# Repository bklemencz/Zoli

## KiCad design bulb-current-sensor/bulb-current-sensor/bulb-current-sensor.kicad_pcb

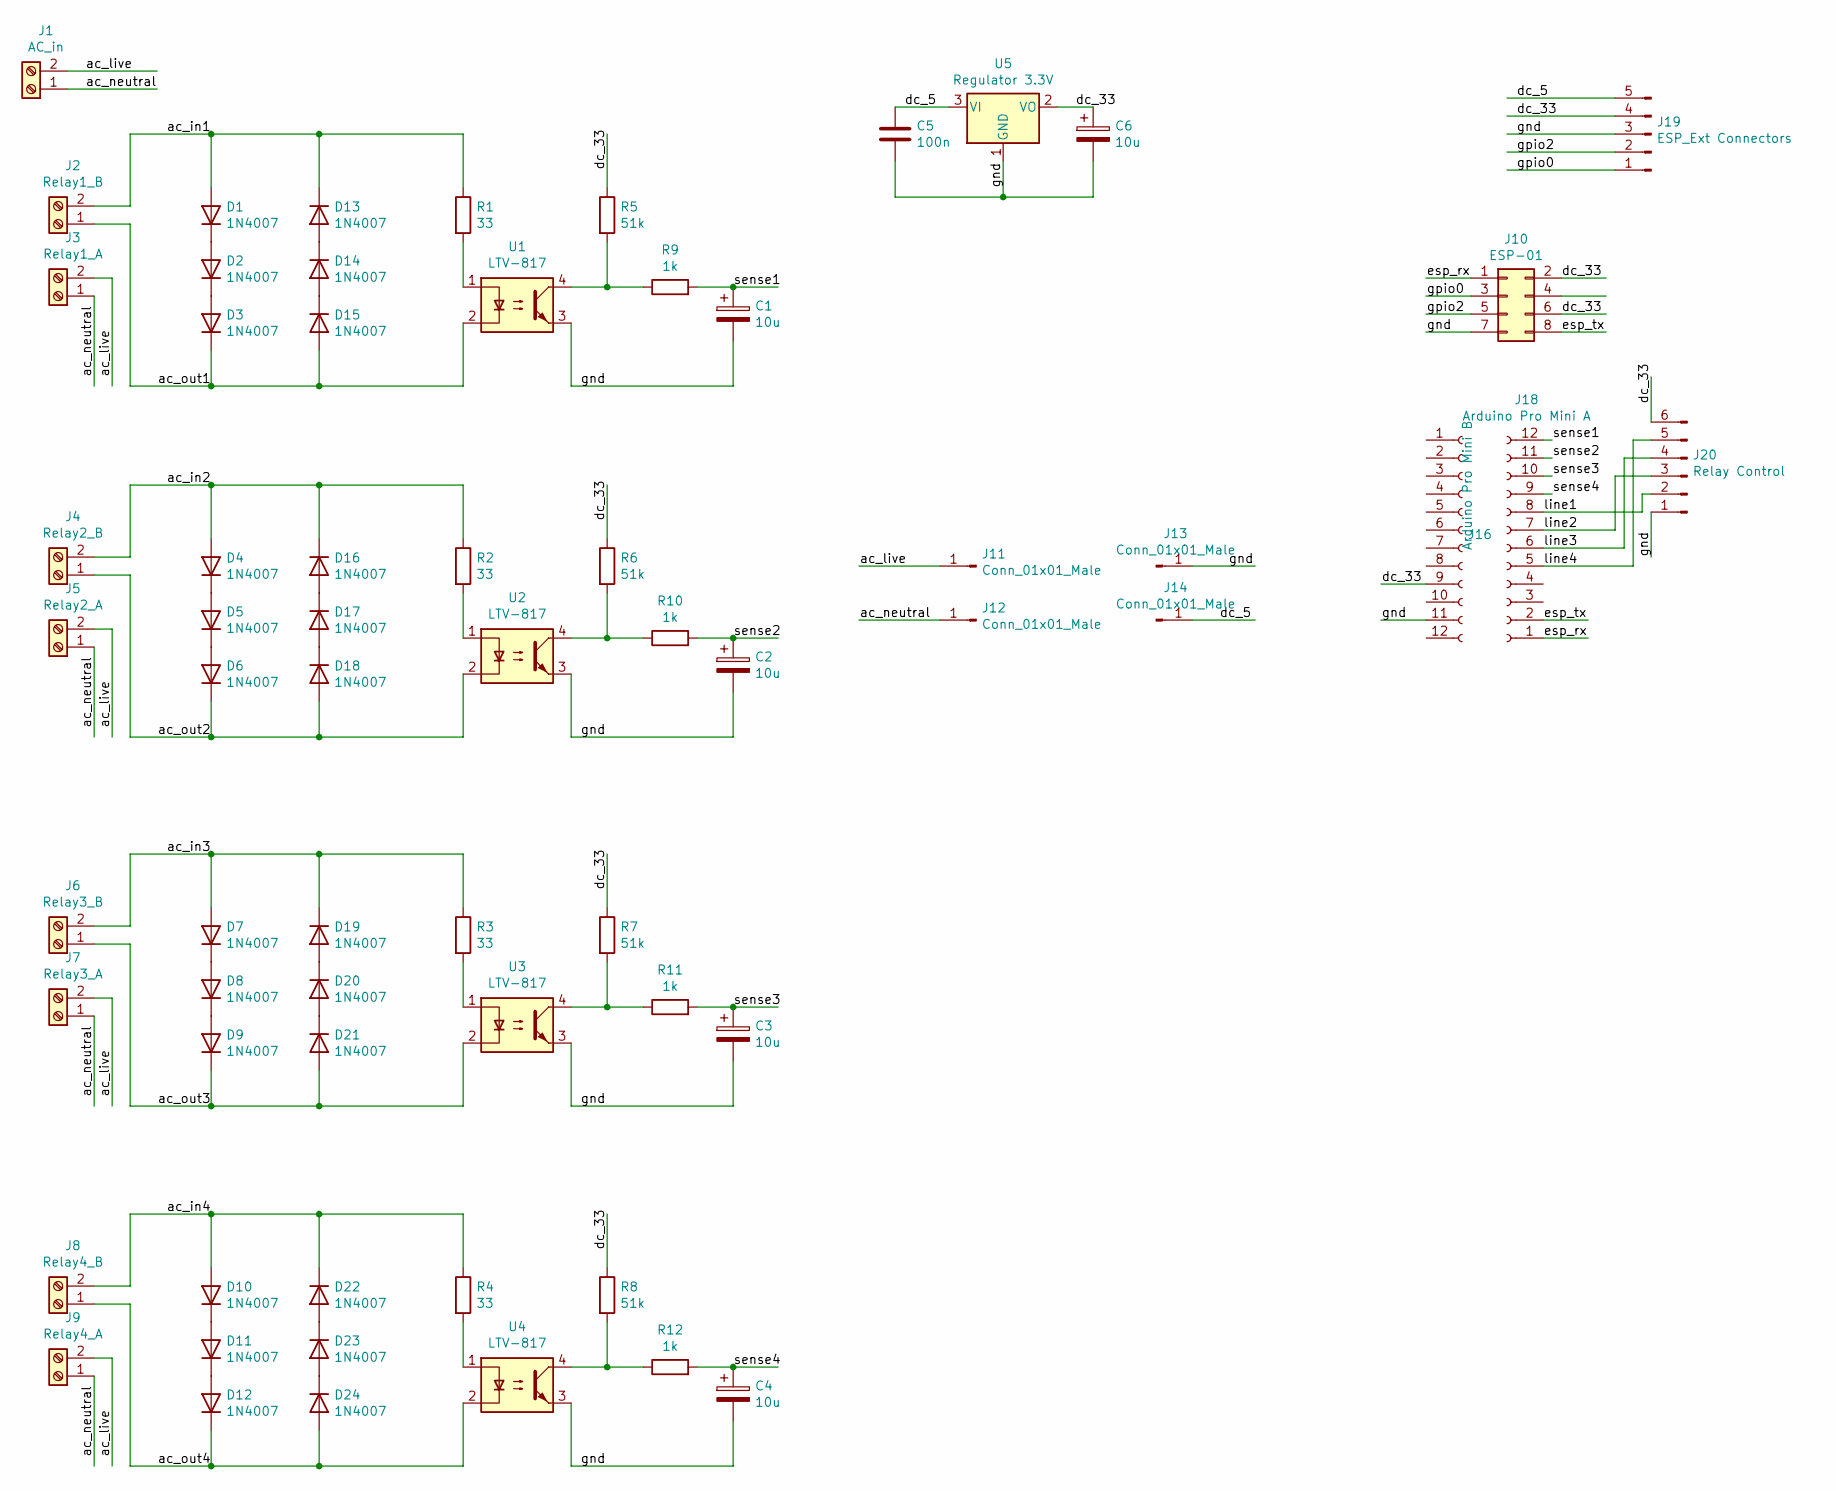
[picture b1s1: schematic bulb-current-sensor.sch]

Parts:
C1, C2, C3, C4: 10u; CP_Radial_D5.0mm_P2.50mm
C5: 100n; C_Disc_D3.0mm_W1.6mm_P2.50mm
C6: 10u; CP_Radial_D4.0mm_P1.50mm
D1, D2, D3, D4, D5, D6, D7, D8, D9, D10, D11, D12, D13, D14, D15, D16, D17, D18, D19, D20, D21, D22, D23, D24: 1N4007; D_DO-41_SOD81_P10.16mm_Horizontal
J1: AC_in; TerminalBlock_bornier-2_P5.08mm
J2: Relay1_B; TerminalBlock_bornier-2_P5.08mm
J3: Relay1_A; TerminalBlock_bornier-2_P5.08mm
J4: Relay2_B; TerminalBlock_bornier-2_P5.08mm
J5: Relay2_A; TerminalBlock_bornier-2_P5.08mm
J6: Relay3_B; TerminalBlock_bornier-2_P5.08mm
J7: Relay3_A; TerminalBlock_bornier-2_P5.08mm
J8: Relay4_B; TerminalBlock_bornier-2_P5.08mm
J9: Relay4_A; TerminalBlock_bornier-2_P5.08mm
J10: ESP-01; PinHeader_2x04_P2.54mm_Vertical
J11, J12, J13, J14: Conn_01x01_Male; PinHeader_1x01_P2.54mm_Vertical
J16: Arduino Pro Mini B; PinHeader_1x12_P2.54mm_Vertical
J18: Arduino Pro Mini A; PinHeader_1x12_P2.54mm_Vertical
J19: ESP_Ext Connectors; PinHeader_1x05_P2.54mm_Vertical
J20: Relay Control; PinHeader_1x06_P2.54mm_Vertical
R1, R2, R3, R4: 33; R_Axial_DIN0207_L6.3mm_D2.5mm_P10.16mm_Horizontal
R5, R6, R7, R8: 51k; R_Axial_DIN0204_L3.6mm_D1.6mm_P7.62mm_Horizontal
R9, R10, R11, R12: 1k; R_Axial_DIN0204_L3.6mm_D1.6mm_P7.62mm_Horizontal
U1, U2, U3, U4: LTV-817; DIP-4_W7.62mm
U5: Regulator 3.3V; TO-220-3_Vertical

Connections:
/ac_in1: D1.2 (A), D13.1 (K), J2.2, R1.1
/ac_in2: D4.2 (A), D16.1 (K), J4.2, R2.1
/ac_in3: D7.2 (A), D19.1 (K), J6.2, R3.1
/ac_in4: D10.2 (A), D22.1 (K), J8.2, R4.1
/ac_live: J1.2, J3.2, J5.2, J7.2, J9.2, J11.1
/ac_neutral: J1.1, J3.1, J5.1, J7.1, J9.1, J12.1
/ac_out1: D3.1 (K), D15.2 (A), J2.1, U1.2
/ac_out2: D6.1 (K), D18.2 (A), J4.1, U2.2
/ac_out3: D9.1 (K), D21.2 (A), J6.1, U3.2
/ac_out4: D12.1 (K), D24.2 (A), J8.1, U4.2
/dc_5: C5.1, J14.1, J19.5, U5.3 (VI)
/dc_33: C6.1, J10.2, J10.6, J16.9, J19.4, J20.6, R5.1, R6.1, R7.1, R8.1, U5.2 (VO)
/esp_rx: J10.1, J18.1
/esp_tx: J10.8, J18.2
/gnd: C1.2, C2.2, C3.2, C4.2, C5.2, C6.2, J10.7, J13.1, J16.11, J19.3, J20.1, U1.3, U2.3, U3.3, U4.3, U5.1 (GND)
/gpio0: J10.3, J19.1
/gpio2: J10.5, J19.2
/line1: J18.8, J20.2
/line2: J18.7, J20.3
/line3: J18.6, J20.4
/line4: J18.5, J20.5
/sense1: C1.1, J18.12, R9.2
/sense2: C2.1, J18.11, R10.2
/sense3: C3.1, J18.10, R11.2
/sense4: C4.1, J18.9, R12.2
unnamed: D1.1 (K), D2.2 (A)
unnamed: D2.1 (K), D3.2 (A)
unnamed: D4.1 (K), D5.2 (A)
unnamed: D5.1 (K), D6.2 (A)
unnamed: D7.1 (K), D8.2 (A)
unnamed: D8.1 (K), D9.2 (A)
unnamed: D10.1 (K), D11.2 (A)
unnamed: D11.1 (K), D12.2 (A)
unnamed: D13.2 (A), D14.1 (K)
unnamed: D14.2 (A), D15.1 (K)
unnamed: D16.2 (A), D17.1 (K)
unnamed: D17.2 (A), D18.1 (K)
unnamed: D19.2 (A), D20.1 (K)
unnamed: D20.2 (A), D21.1 (K)
unnamed: D22.2 (A), D23.1 (K)
unnamed: D23.2 (A), D24.1 (K)
unnamed: R1.2, U1.1
unnamed: R2.2, U2.1
unnamed: R3.2, U3.1
unnamed: R4.2, U4.1
unnamed: R5.2, R9.1, U1.4
unnamed: R6.2, R10.1, U2.4
unnamed: R7.2, R11.1, U3.4
unnamed: R8.2, R12.1, U4.4

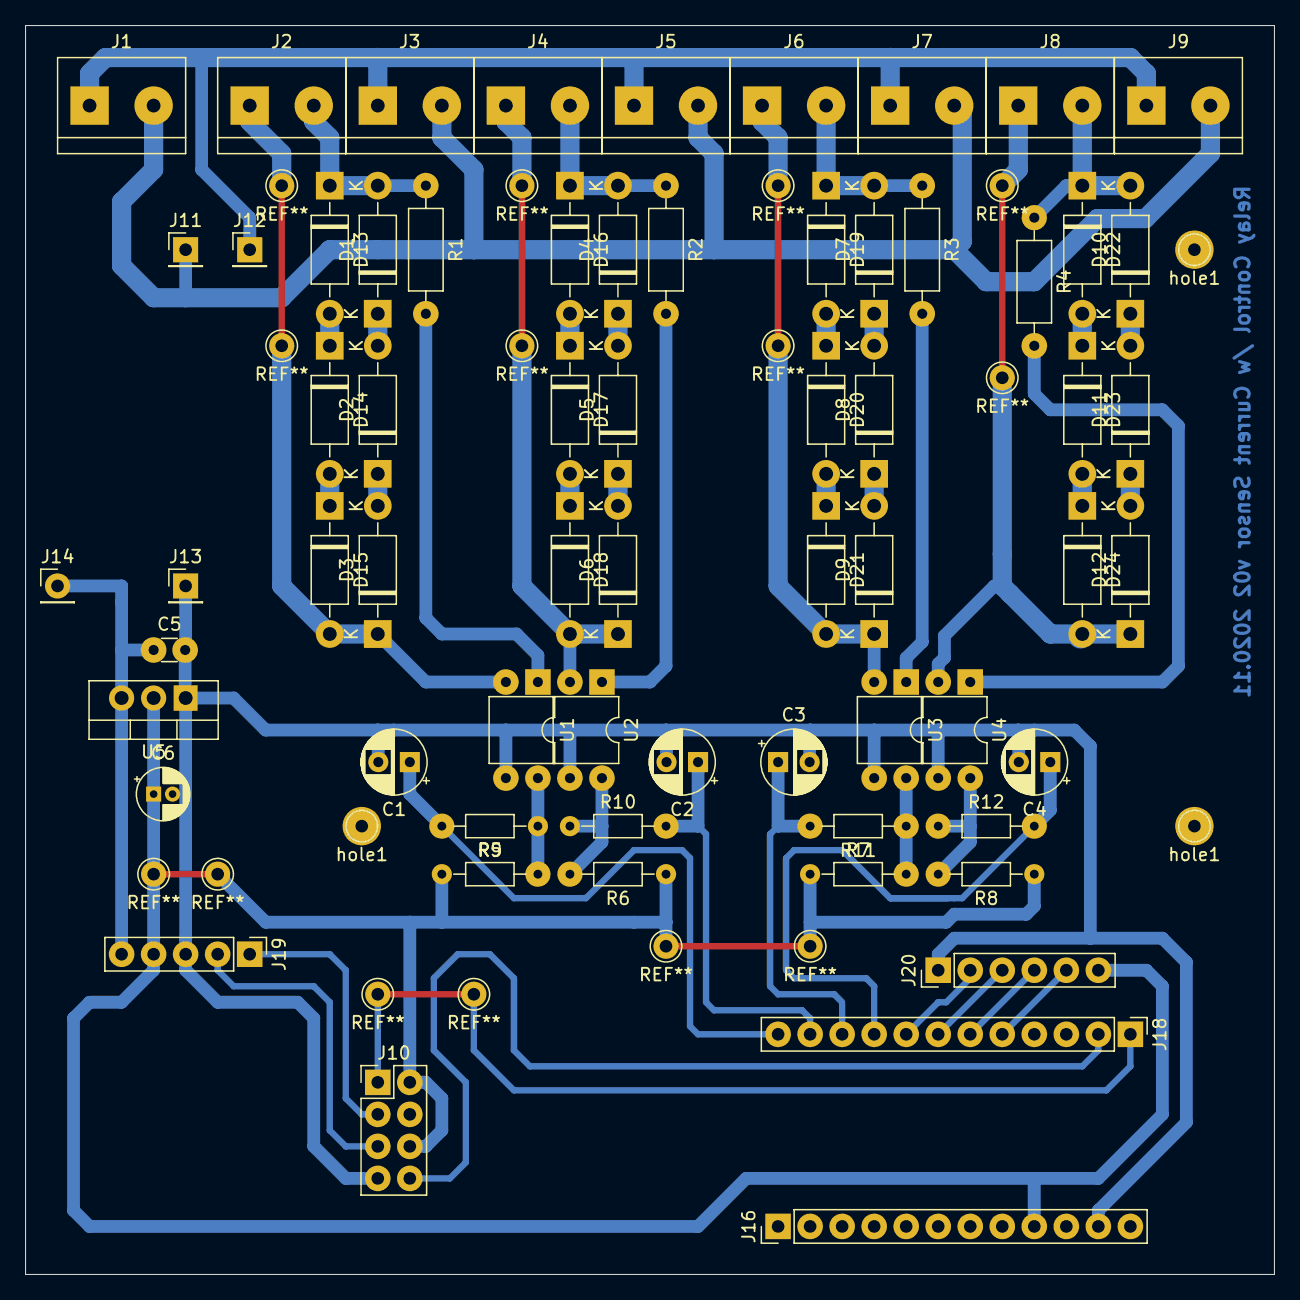
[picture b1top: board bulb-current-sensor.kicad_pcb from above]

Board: 2 copper layers, 99.1 x 99.1 mm, 68 parts (0 on the bottom side), 49 nets.

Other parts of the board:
hole1, hole1#2, hole1#3: Pin_D1.0mm_L10.0mm

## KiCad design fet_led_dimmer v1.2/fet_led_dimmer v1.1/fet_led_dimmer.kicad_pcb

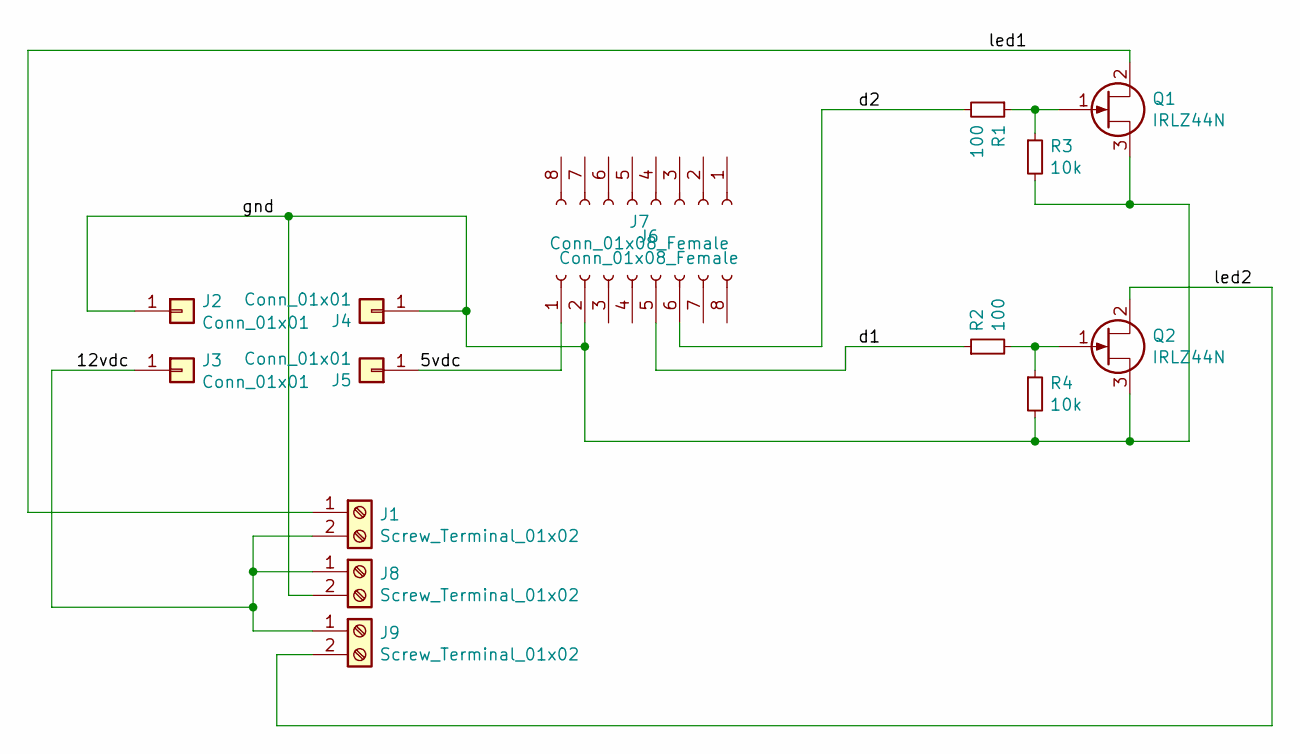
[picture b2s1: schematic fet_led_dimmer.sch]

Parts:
J1, J8, J9: Screw_Terminal_01x02; TerminalBlock_bornier-2_P5.08mm
J2, J3, J4, J5: Conn_01x01; PinHeader_1x01_P2.54mm_Vertical
J6, J7: Conn_01x08_Female; PinHeader_1x08_P2.54mm_Vertical
Q1, Q2: IRLZ44N; TO-220-3_Vertical
R1, R2: 100; R_Axial_DIN0204_L3.6mm_D1.6mm_P5.08mm_Horizontal
R3, R4: 10k; R_Axial_DIN0204_L3.6mm_D1.6mm_P5.08mm_Horizontal

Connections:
/5vdc: J5.1, J6.1
/12vdc: J1.2, J3.1, J8.1, J9.1
/d1: J6.5, R2.1
/d2: J6.6, R1.2
/gnd: J2.1, J4.1, J6.2, J8.2, Q1.3 (S), Q2.3 (S), R3.2, R4.2
/led1: J1.1, Q1.2 (D)
/led2: J9.2, Q2.2 (D)
unnamed: Q1.1 (G), R1.1, R3.1
unnamed: Q2.1 (G), R2.2, R4.1

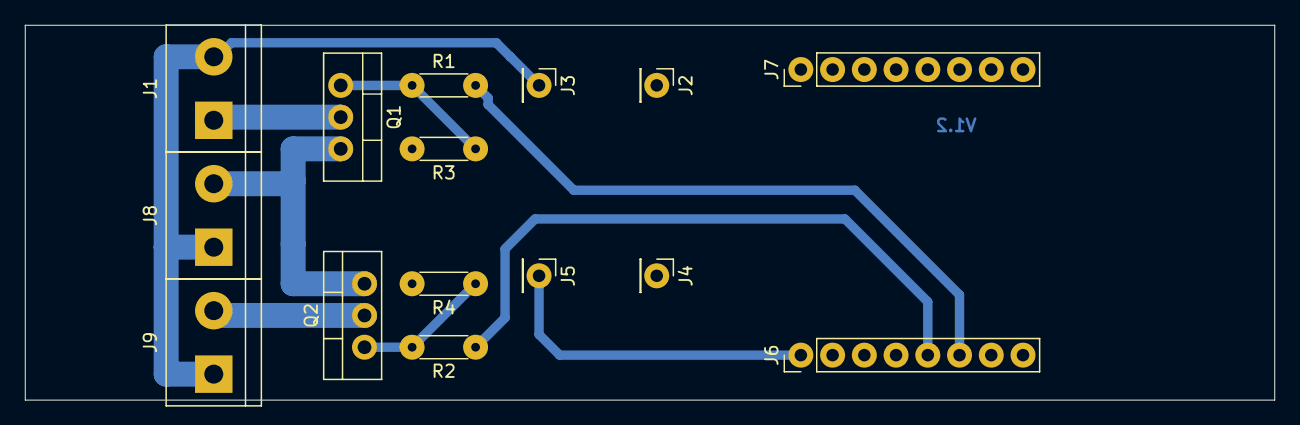
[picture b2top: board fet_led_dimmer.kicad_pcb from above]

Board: 2 copper layers, 100.0 x 30.0 mm, 15 parts (0 on the bottom side), 9 nets.

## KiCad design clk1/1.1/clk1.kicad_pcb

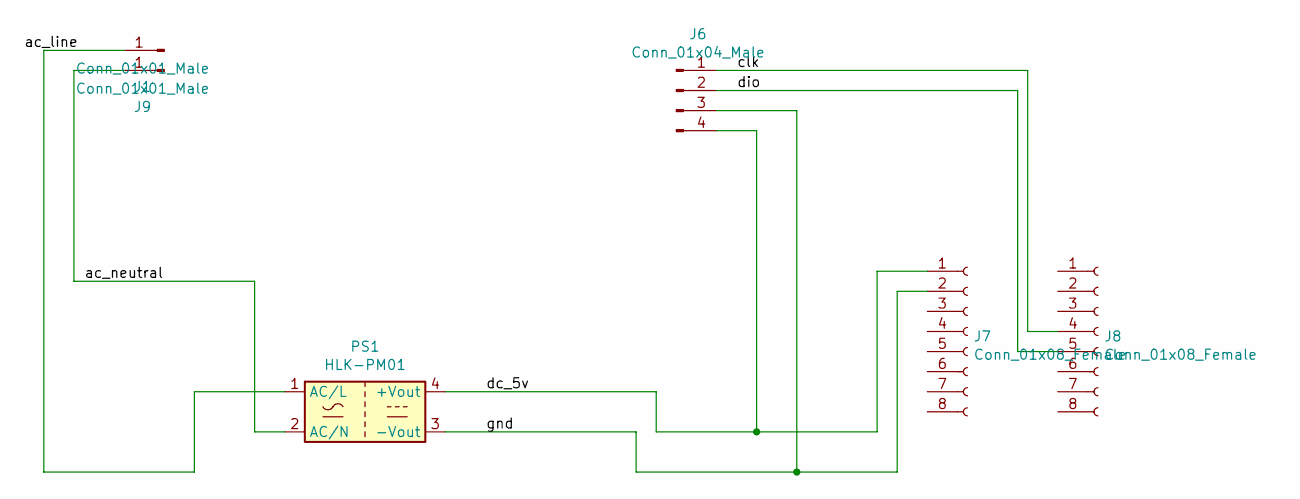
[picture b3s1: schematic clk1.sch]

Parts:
J1, J9: Conn_01x01_Male; Pin_D1.0mm_L10.0mm
J6: Conn_01x04_Male; PinHeader_1x04_P2.54mm_Vertical
J7, J8: Conn_01x08_Female; PinSocket_1x08_P2.54mm_Vertical
PS1: HLK-PM01; Converter_ACDC_HiLink_HLK-PMxx

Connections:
/ac_neutral: J9.1, PS1.2 (AC/N)
/clk: J6.1, J8.4
/dc_5v: J6.4, J7.1, PS1.4 (+Vout)
/dio: J6.2, J8.5
/gnd: J6.3, J7.2, PS1.3 (-Vout)
unnamed: J1.1, PS1.1 (AC/L)

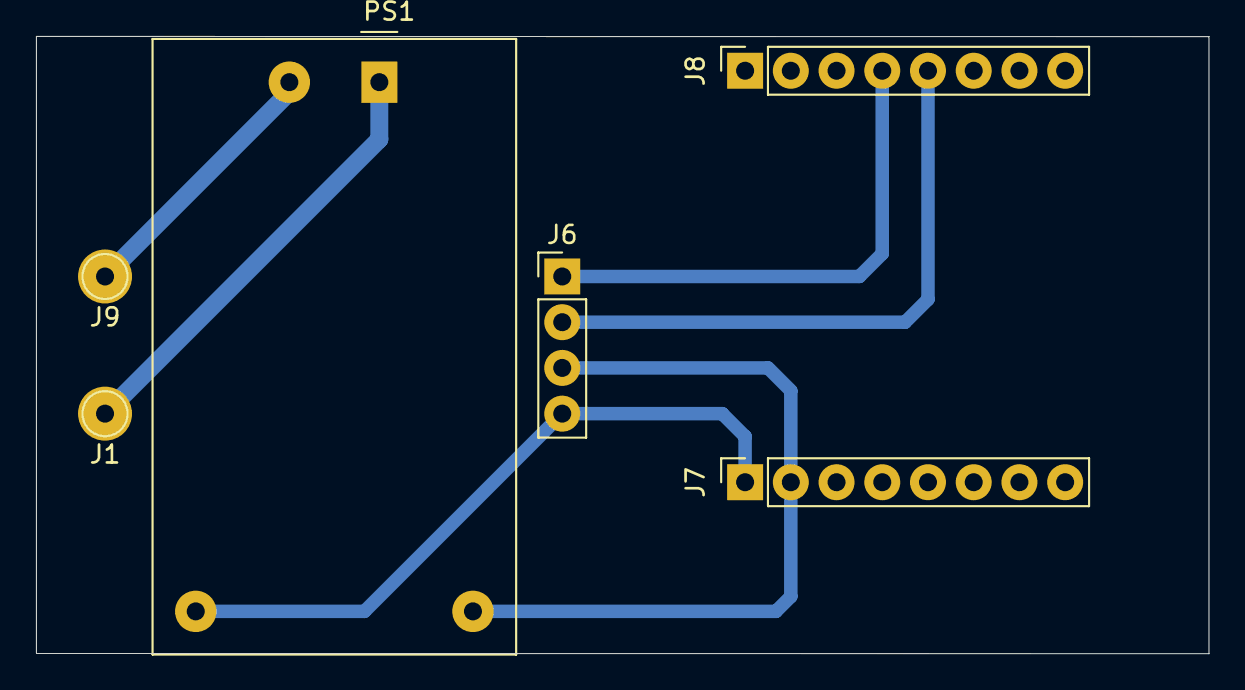
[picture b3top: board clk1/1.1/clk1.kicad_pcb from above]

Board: 2 copper layers, 65.1 x 34.3 mm, 6 parts (0 on the bottom side), 6 nets.

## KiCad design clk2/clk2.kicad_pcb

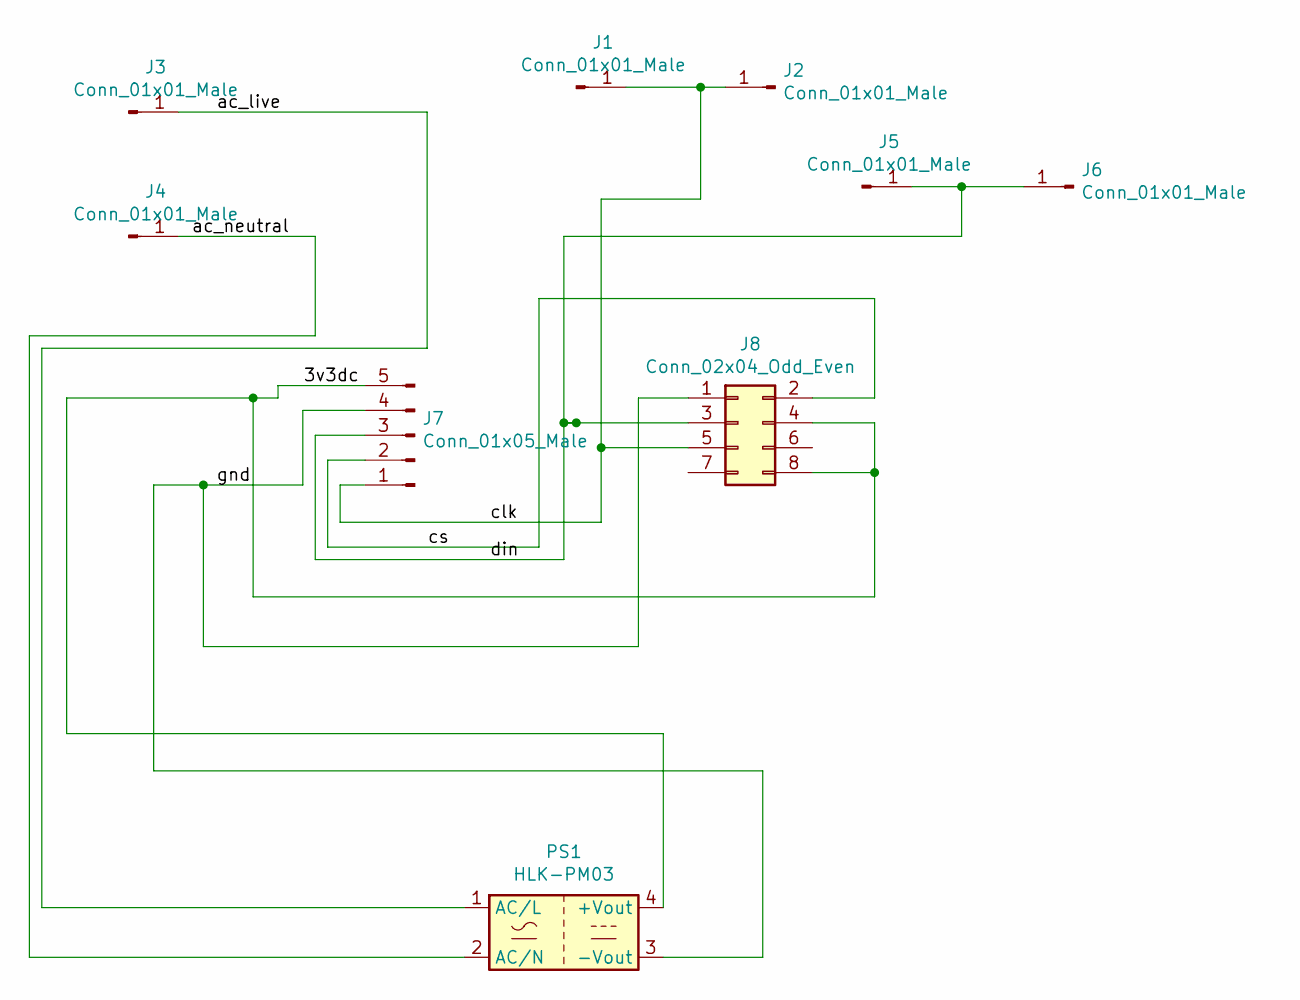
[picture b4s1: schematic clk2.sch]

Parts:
J1, J2, J3, J4, J5, J6: Conn_01x01_Male; Pin_D1.0mm_L10.0mm
J7: Conn_01x05_Male; PinHeader_1x05_P2.54mm_Vertical
J8: Conn_02x04_Odd_Even; PinSocket_2x04_P2.54mm_Vertical
PS1: HLK-PM03; Converter_ACDC_HiLink_HLK-PMxx

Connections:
/3v3dc: J7.5, J8.4, J8.8, PS1.4 (+Vout)
/ac_live: J3.1, PS1.1 (AC/L)
/ac_neutral: J4.1, PS1.2 (AC/N)
/clk: J1.1, J2.1, J7.1, J8.5
/cs: J7.2, J8.2
/din: J5.1, J6.1, J7.3, J8.3
/gnd: J7.4, J8.1, PS1.3 (-Vout)

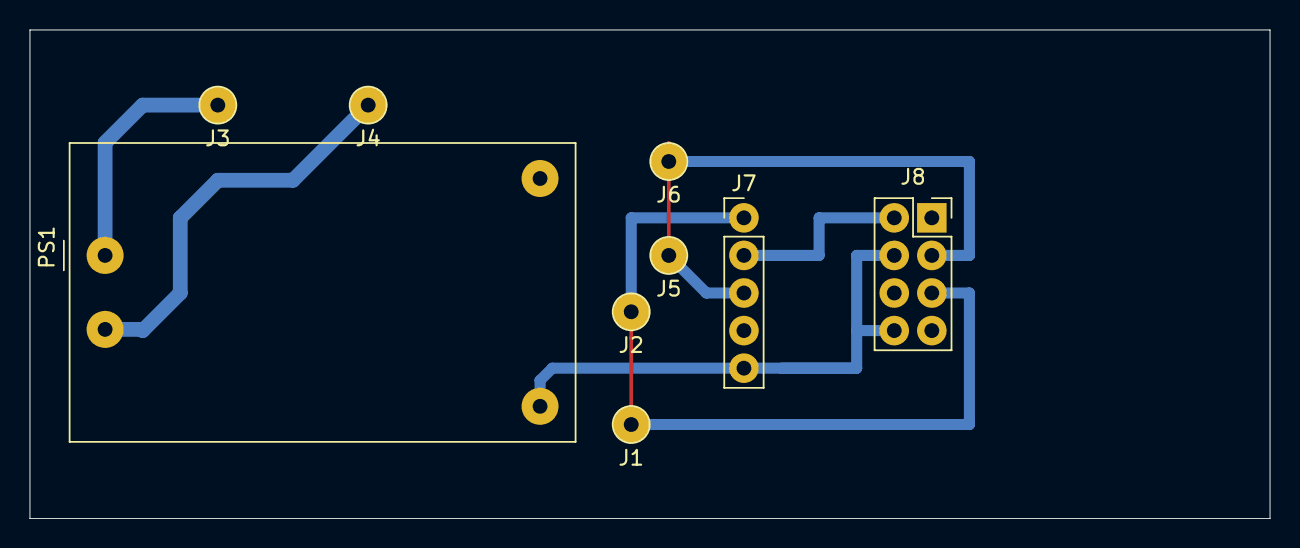
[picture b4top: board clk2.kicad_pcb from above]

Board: 2 copper layers, 83.8 x 33.0 mm, 9 parts (0 on the bottom side), 7 nets.

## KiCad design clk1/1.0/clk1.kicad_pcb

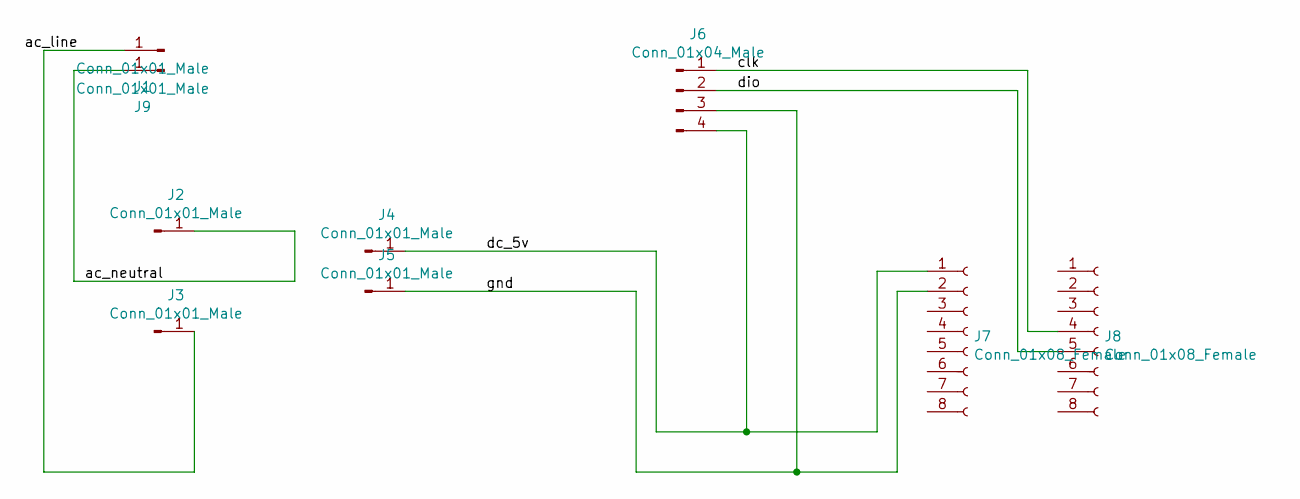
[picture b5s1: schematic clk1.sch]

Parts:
J1, J2, J3, J4, J5, J9: Conn_01x01_Male; Pin_D1.0mm_L10.0mm
J6: Conn_01x04_Male; PinHeader_1x04_P2.54mm_Vertical
J7, J8: Conn_01x08_Female; PinSocket_1x08_P2.54mm_Vertical

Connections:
/ac_neutral: J2.1, J9.1
/clk: J6.1, J8.4
/dc_5v: J4.1, J6.4, J7.1
/dio: J6.2, J8.5
/gnd: J5.1, J6.3, J7.2
unnamed: J1.1, J3.1

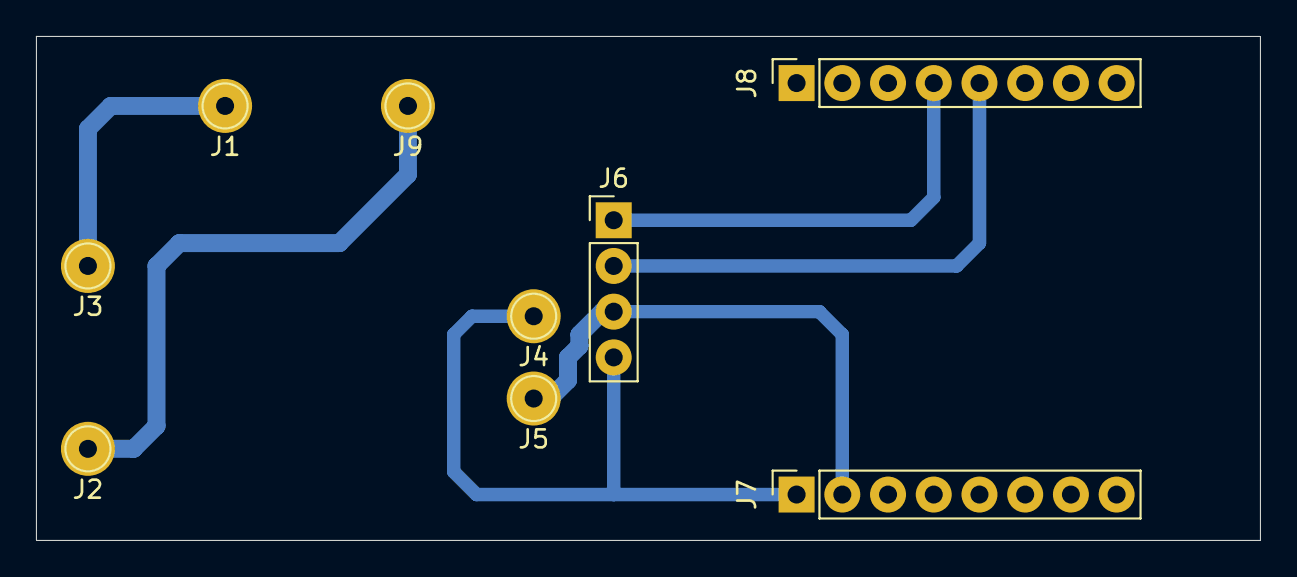
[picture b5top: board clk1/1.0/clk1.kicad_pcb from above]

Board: 2 copper layers, 68.0 x 28.0 mm, 9 parts (0 on the bottom side), 6 nets.

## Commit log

2020-12-06 Init
2020-12-31 clk1.1
2021-01-28 Dimmer Update
